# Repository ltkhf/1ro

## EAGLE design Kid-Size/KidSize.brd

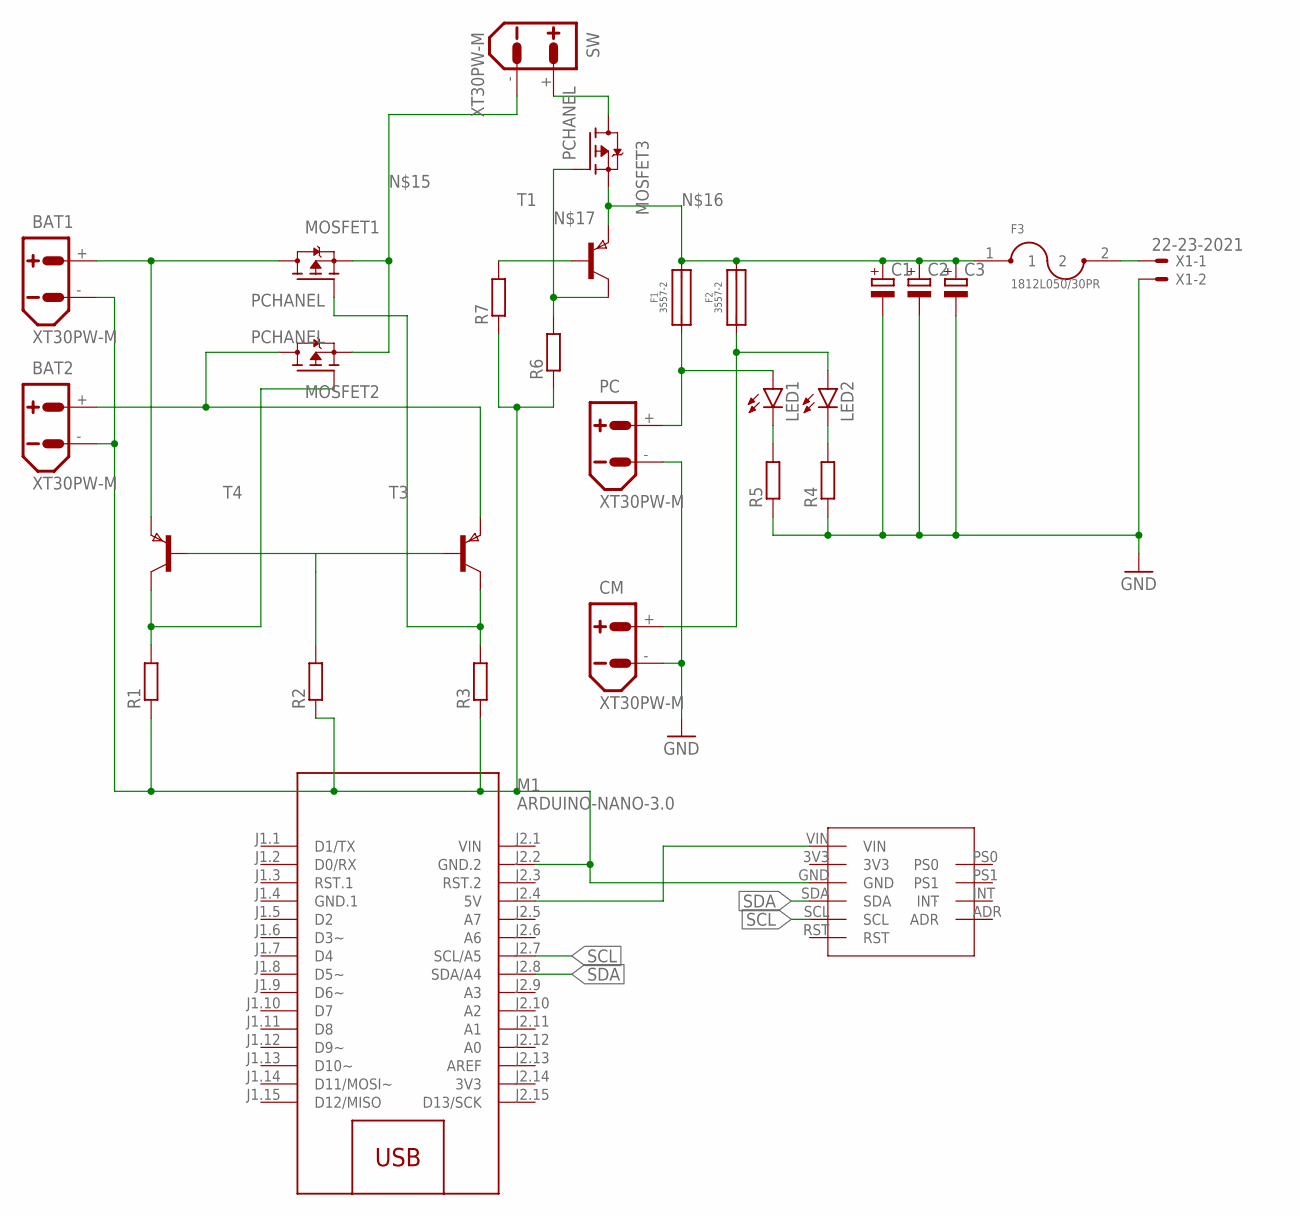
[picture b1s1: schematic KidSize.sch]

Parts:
BAT1, BAT2: XT30PW-M
C1, C2, C3: CPOL-EU150CLZ-1014; 150CLZ-1014
CM: XT30PW-M
F1, F2: 3557-2
F3: 1812L050/30PR; FUSM4632X75
LED1, LED2: LEDCHIP-LED0805; CHIP-LED0805
M1: ARDUINO-NANO-3.0
MOSFET1, MOSFET2, MOSFET3: PCHANEL; TO252
PC: XT30PW-M
R1, R2, R3: R-EU_R1206; R1206
R4, R5, R6, R7: R-EU_M0805; M0805
SW: XT30PW-M
T1, T3, T4: PNPSOT23; SOT-23
U$1: BNO055_BNO055
X1: 22-23-2021

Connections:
3V3: M1.J2.14 (3V3)
GND: BAT1.-, BAT2.-, C1.-, C2.-, C3.-, CM.-, M1.J2.2 (GND.2), PC.-, R1.1, R2.1, R3.1, R4.1, R5.1, R6.1, R7.1, U$1.GND, X1.2
GND.1: M1.J1.4 (GND.1)
unnamed: BAT1.+, MOSFET1.3 (D), T4.2 (E)
unnamed: MOSFET2.1 (G), R1.2, T4.1 (C)
unnamed: R2.2, T3.3 (B), T4.3 (B)
unnamed: M1.J2.4 (5V), U$1.VIN
unnamed: F1.1, F1.2 (1), LED1.A, PC.+
unnamed: CM.+, F2.1, F2.2 (1), LED2.A
unnamed: R7.2, T1.3 (B)
unnamed: MOSFET1.1 (G), R3.2, T3.1 (C)
unnamed: BAT2.+, MOSFET2.3 (D), T3.2 (E)
unnamed: LED1.C, R5.2
unnamed: MOSFET3.3 (D), SW.+
unnamed: LED2.C, R4.2
unnamed: F3.2, X1.1
unnamed: MOSFET1.2 (S), MOSFET2.2 (S), SW.-
unnamed: C1.+, C2.+, C3.+, F1.3 (2), F1.4 (2), F2.3 (2), F2.4 (2), F3.1, MOSFET3.2 (S), T1.2 (E)
unnamed: MOSFET3.1 (G), R6.2, T1.1 (C)
SCL: M1.J2.7 (SCL/A5), U$1.SCL
SDA: M1.J2.8 (SDA/A4), U$1.SDA
VIN: M1.J2.1 (VIN)

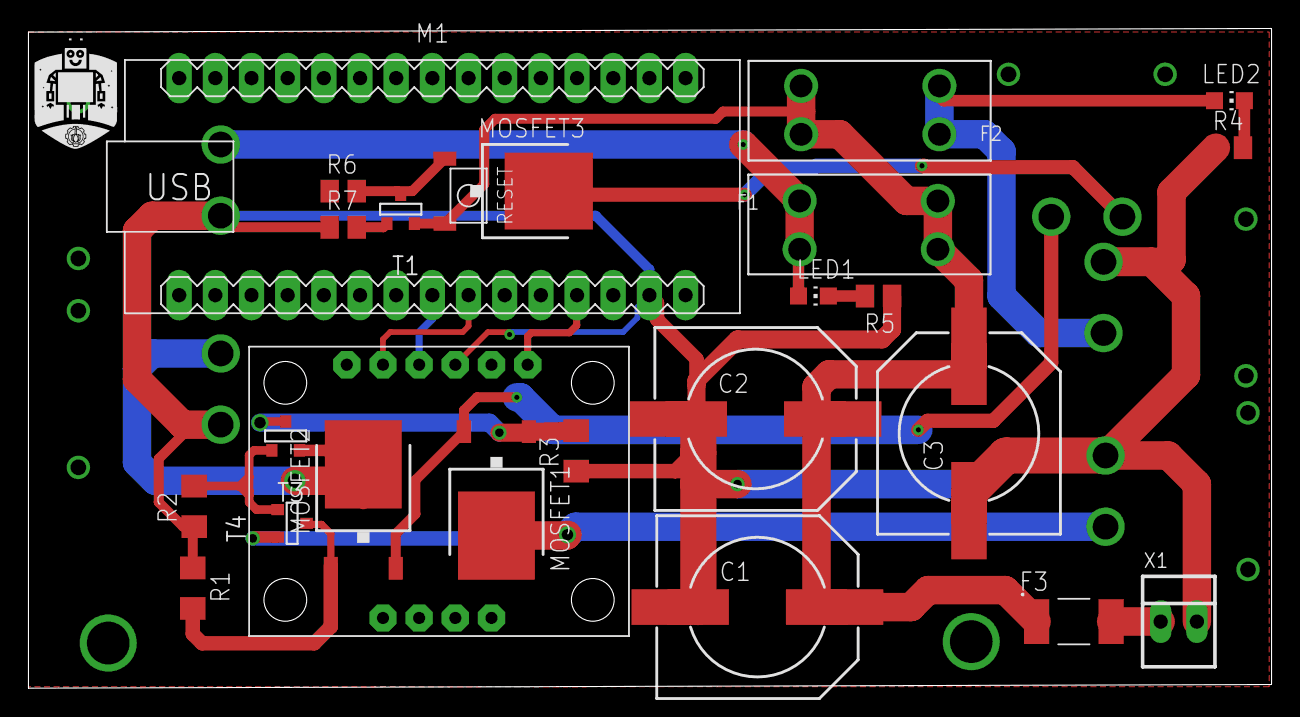
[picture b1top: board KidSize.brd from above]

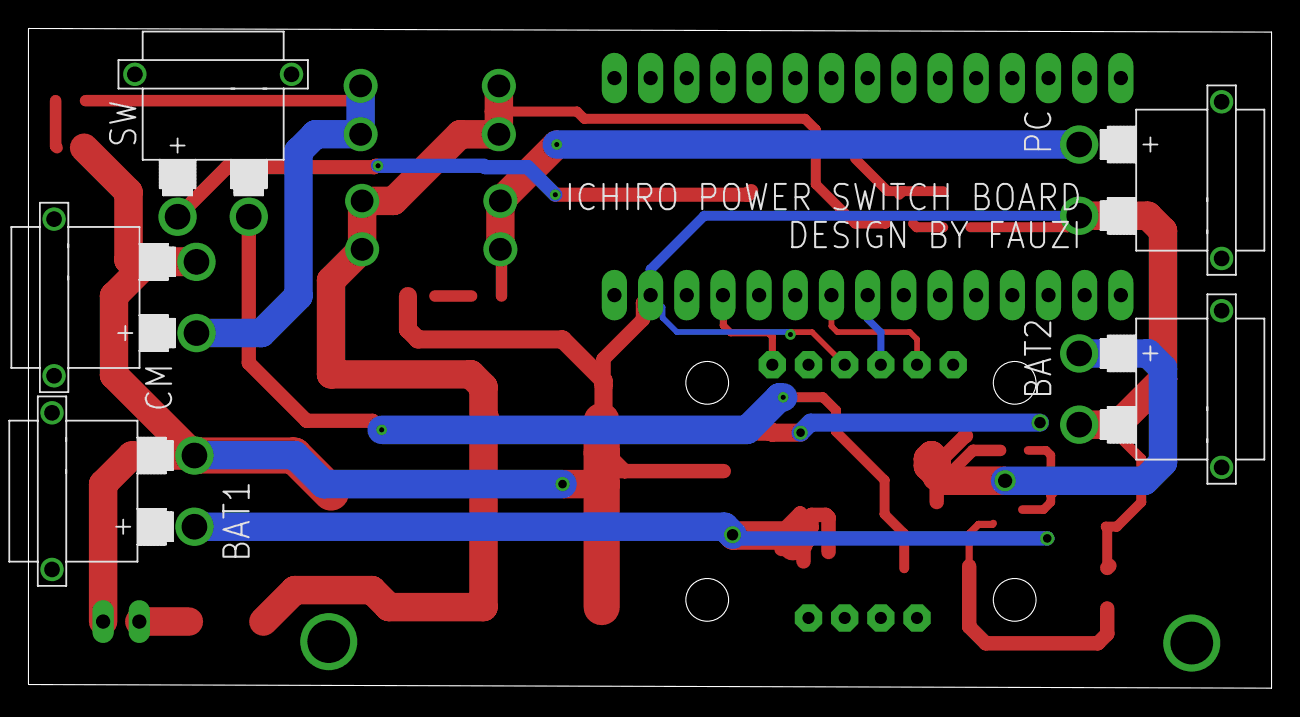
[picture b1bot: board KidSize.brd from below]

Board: 2 copper layers, 87.3 x 46.3 mm, 29 parts (5 on the bottom side), 19 nets.

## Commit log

2023-09-22 Add files via upload
    ini yang ver. saya tapi gatau bener apa engga, semangat yah

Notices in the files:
parts and their libraries:
diy-modules: Released under the Creative Commons Attribution 4.0 International License: http://creativecommons.org/licenses/by/4.0
